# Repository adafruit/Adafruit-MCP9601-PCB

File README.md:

## Adafruit MCP9601 (MCP96L01) I2C Thermocouple Amplifier - STEMMA QT / Qwiic PCB

<a href="http://www.adafruit.com/products/5165"><br/>
Click here to purchase one from the Adafruit shop</a>

PCB files for the Adafruit MCP9601 (MCP96L01) I2C Thermocouple Amplifier - STEMMA QT / Qwiic. 

Format is EagleCAD schematic and board layout
* https://www.adafruit.com/product/5165

### Description

Thermocouples are very sensitive, requiring a good amplifier with a cold-compensation reference. The Adafruit MCP9601 I2C Thermocouple Breakout (a.k.a MCP96L01) does all that for you and can be easily interfaced with any microcontroller or single-board computer with I2C. Inside, the chip handles all the analog stuff for you, and can interface with just about any thermocouple type: K, J, T, N, S, E, B, and R types are all supported! You can also set various alerts for over/under temperature, and read the thermocouple (hot) temperature and the chip (cold) temperature. All this over common I2C.

This breakout board has the chip itself, a 3.3V regulator and level shifting circuitry, all assembled and tested. Works great with 3.3V or 5V logic. Comes with a 2-pin terminal block (for connecting to the thermocouple) and pin header (to plug into any breadboard or perfboard). Match it up with our 1m K-type thermocouple.

Works with any K, J, T, N, S, E, B, and R type thermocouple
Datasheet rated for:
K Type: -200°C to +1372°C
J Type: -150°C to +1200°C
T Type: -200°C to +400°C
N Type: -150°C to +1300°C
E Type: -200°C to +1000°C
S Type: +250°C to +1664°C
B Type: +1000°C to +1800°C
R Type: +250°C to +1664°C
Resolution of ±0.0625 °C - note that this is just resolution of the ADC iytoyt, not accuracy
We use the MCP96L01 in this breakout which has ±2.0°C/±4.0°C (typ./max.) thermocouple accuracy (which is not including the innate inaccuracy of thermocouples, K thermocouples have about ±2°C to ±6°C accuracy)
Internal temperature reading ('cold junction'
3.3 to 5v power supply and logic level compliant
I2C data connection
Additionally, since it speaks I2C you can easily connect it up with two wires (plus power and ground!).  We've even included SparkFun qwiic compatible STEMMA QT connectors for the I2C bus so you don't even need to solder! Use a plug-and-play STEMMA QT cable to get temperature data ASAP. QT Cable is not included, but we have a variety in the shop

Comes assembled and tested. Some soldering is required to attach the terminal block or header to the breakout PCB. The header is only required if you want to use it in a breadboard.

### License

Adafruit invests time and resources providing this open source design, please support Adafruit and open-source hardware by purchasing products from [Adafruit](https://www.adafruit.com)!

Designed by Limor Fried/Ladyada for Adafruit Industries.

Creative Commons Attribution/Share-Alike, all text above must be included in any redistribution. 
See license.txt for additional details.

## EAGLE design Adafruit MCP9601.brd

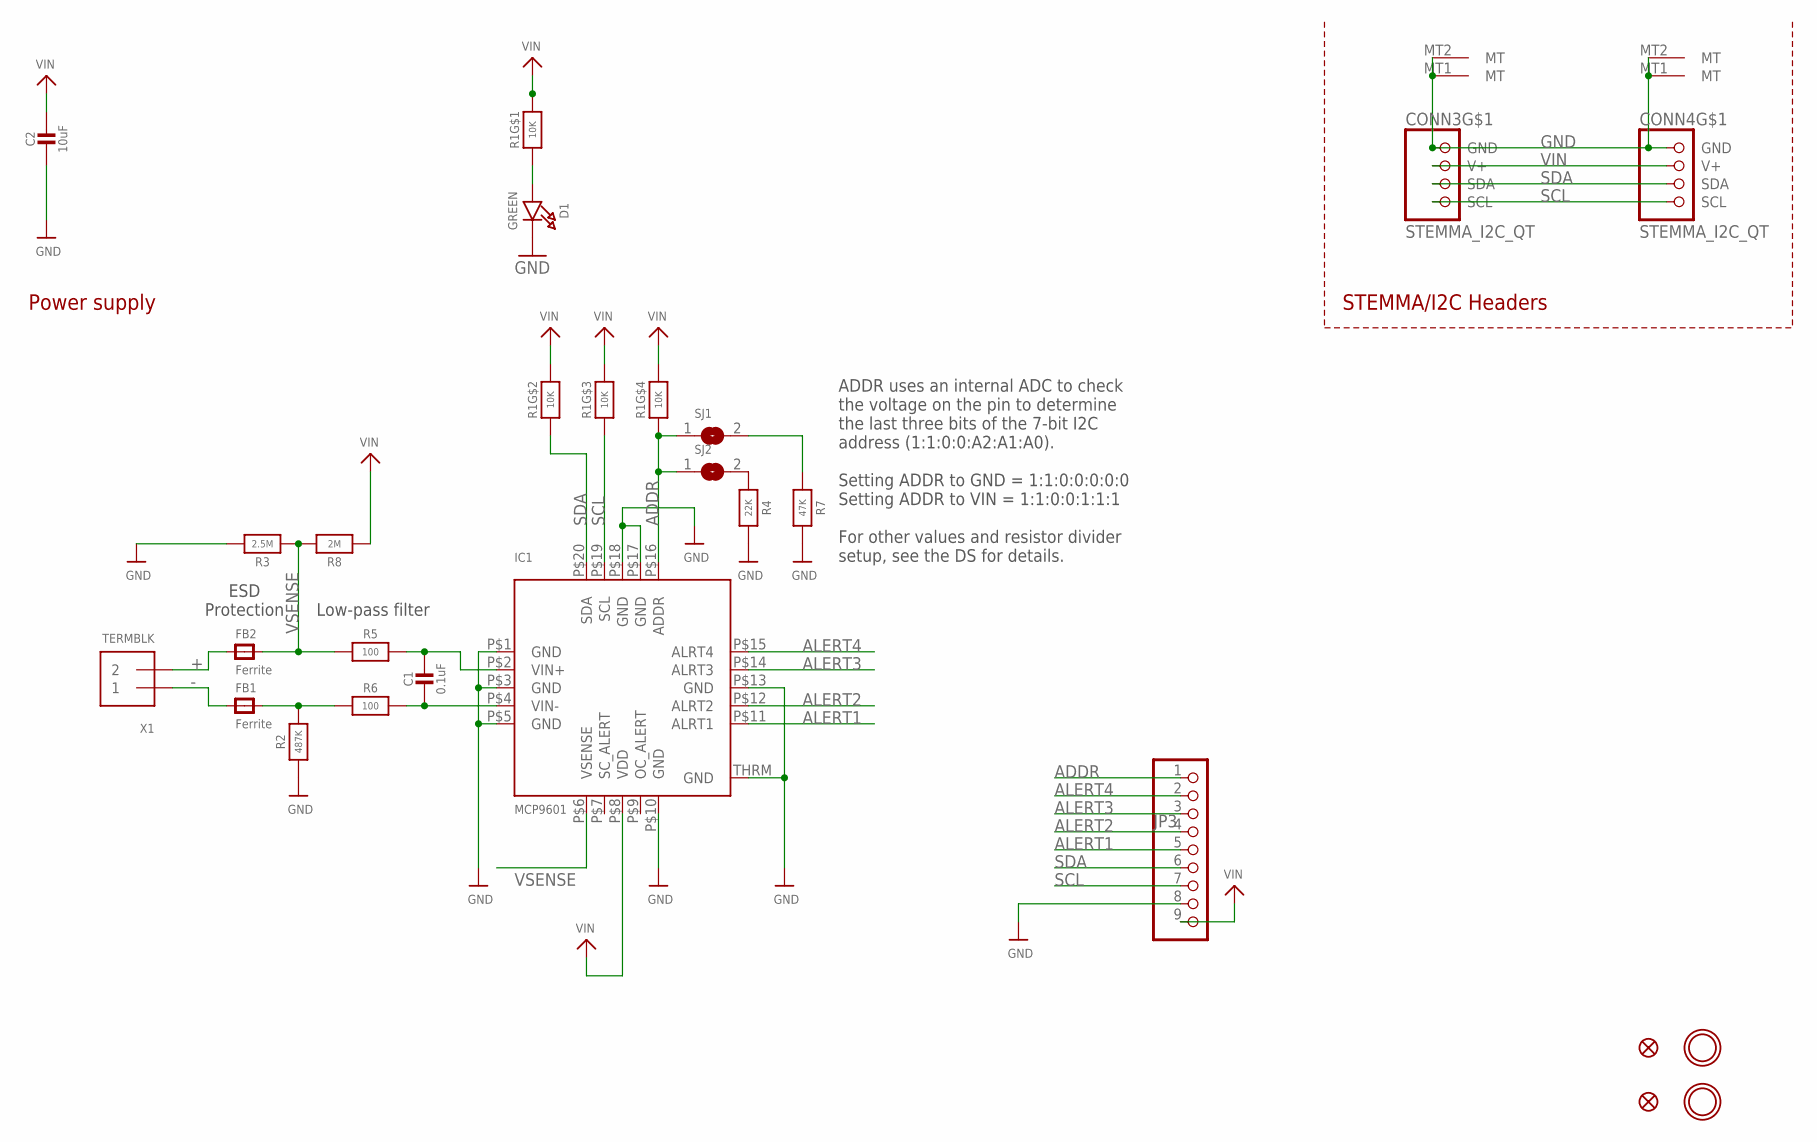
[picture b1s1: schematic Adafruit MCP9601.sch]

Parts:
C1: 0.1uF; 0603-NO
C2: 10uF; 0805-NO
CONN3, CONN4: STEMMA_I2C_QT; JST_SH4
D1: GREEN; CHIPLED_0603_NOOUTLINE
FB1, FB2: Ferrite; 0603-NO
FID3, FID4: FIDUCIAL_1MM
IC1: MCP9601; VQFN20_5MM
JP3: HEADER-1X970MIL; 1X09_ROUND_70
R1: 10K; RESPACK_4X0603
R2: 487K; 0603-NO
R3: 2.5M; 0603-NO
R4: 22K; 0603-NO
R5, R6: 100; 0603-NO
R7: 47K; 0603-NO
R8: 2M; 0603-NO
SJ1, SJ2: SOLDERJUMPER; SOLDERJUMPER_ARROW_NOPASTE
U$33, U$34: MOUNTINGHOLE2.5; MOUNTINGHOLE_2.5_PLATED
X1: TERMBLK; TERMBLOCK_1X2-3.5MM

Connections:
+: FB2.1, X1.2
-: FB1.1, X1.1
ADDR: IC1.P$16 (ADDR), JP3.1, R1.4 (1), SJ1.1, SJ2.1
ALERT1: IC1.P$11 (ALRT1), JP3.5
ALERT2: IC1.P$12 (ALRT2), JP3.4
ALERT3: IC1.P$14 (ALRT3), JP3.3
ALERT4: IC1.P$15 (ALRT4), JP3.2
GND: C2.2, CONN3.1 (GND), CONN3.MT1 (MT), CONN3.MT2 (MT), CONN4.1 (GND), CONN4.MT1 (MT), CONN4.MT2 (MT), D1.C, IC1.P$1 (GND), IC1.P$3 (GND), IC1.P$5 (GND), IC1.P$10 (GND), IC1.P$13 (GND), IC1.P$17 (GND), IC1.P$18 (GND), IC1.THRM (GND), JP3.8, R2.1, R3.2, R4.2, R7.2
unnamed: C1.1, IC1.P$2 (VIN+), R5.2
unnamed: D1.A, R1.1
unnamed: C1.2, IC1.P$4 (VIN-), R6.2
unnamed: FB1.2, R2.2, R6.1
unnamed: R7.1, SJ1.2
unnamed: R4.1, SJ2.2
SCL: CONN3.4 (SCL), CONN4.4 (SCL), IC1.P$19 (SCL), JP3.7, R1.3 (1)
SDA: CONN3.3 (SDA), CONN4.3 (SDA), IC1.P$20 (SDA), JP3.6, R1.2 (1)
VIN: C2.1, CONN3.2 (V+), CONN4.2 (V+), IC1.P$8 (VDD), JP3.9, R1.5 (2), R1.6 (2), R1.7 (2), R1.8 (2), R8.1
VSENSE: FB2.2, IC1.P$6 (VSENSE), R3.1, R5.1, R8.2

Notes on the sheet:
STEMMA/I2C Headers
Power supply
ADDR uses an internal ADC to check the voltage on the pin to determine the last three bits of the 7-bit I2C address (1:1:0:0:A2:A1:A0). Setting ADDR to GND = 1:1:0:0:0:0:0 Setting ADDR to VIN = 1:1:0:0:1:1:1 For other values and resistor divider setup, see the DS for details.
Low-pass filter
ESD Protection

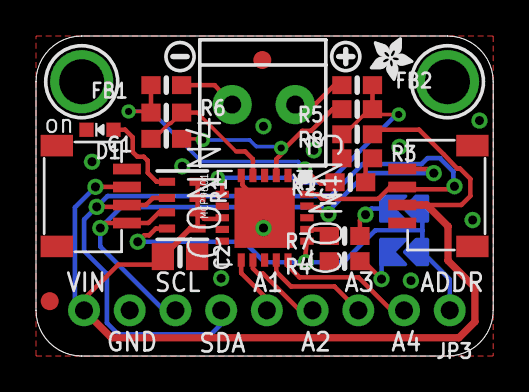
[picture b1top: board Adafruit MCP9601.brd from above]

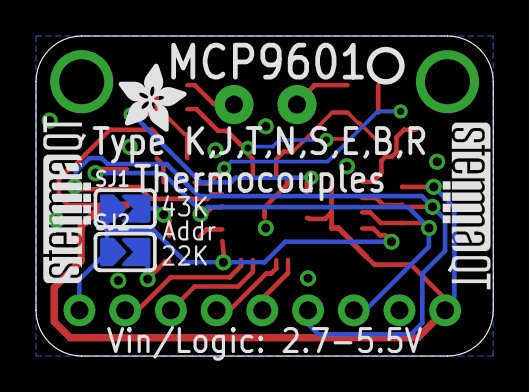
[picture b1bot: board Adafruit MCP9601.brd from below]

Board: 2 copper layers, 25.4 x 17.8 mm, 31 parts (6 on the bottom side), 18 nets.

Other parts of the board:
U$16: ADAFRUIT_2.5MM
U$17: SYMBOL_PLUS
U$18: SYMBOL_MINUS
U$20: ADAFRUIT_3.5MM
U$40: PCBFEAT-REV-040
U$41, U$42: STEMMAQT

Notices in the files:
parts and their libraries:
microbuilder: This work is placed in the public domain, and may be freely used for commercial and non-commercial work with the following conditions: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
